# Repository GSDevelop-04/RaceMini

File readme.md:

<br />
<p align="center">
   
   <br/>
   Véhicule autonome au 1/10
   1/10 self driving car
</p>

##    1) Introduction

RaceMini est un véhicule au 1/10 d'étude sur la conduite autonome.
cliquer pour voir la vidéo sur youtube:

Le véhicule peut être piloté par un smartphone via une application Android et peut fonctionner en automatique ou manuel. Il utilise la reconnaissance des marquages au sol via la transformée de Hough sur une caméra openMV M7 ou H7 

<p align="center">
 
</p>

Le modèle est entierement imprimable en 3D

**Dans le dépot RaceMini vous trouverez :**

* les fichiers CAO, STL pour imprimantes 3D 20 x 20 cm ou 30 x 30 cm
* L'APK Android pour le téléphone
* Le source ESP32 pour IDE Arduino
* Le source Python pour L'OpenMV

Non obligatoire:
* Les fichiers kiCad pour la fabrication d'un circuit imprimé: il rationalise le câblage avec des connecteurs pour chaque élément du système ( carte variateur, alim 5V, camera, écran )
* Des examples de traitement de l'image (transformée de Hough et régréssion) en java script (juste pour comprendre, non utilisés dans RaceMini)

L'ensemble est sous licence **CC BY-NC-SA**

**Les éléments suivants sont nécessaires:**

* Caméra OpenMV H7 (M7 possible) **attention à l'objectif le 2,8 mm d'origine possède un champ de vision un peu limité préférer un 2 ou 2.2 mm**
* ESP32 ( Il existe de nombreux modules le CI est prévu pour un ESP32 DEVKIT V1: 30 broches)
* Carte variateur (la carte DRI0042 dispose d'une sortie 5V régulée)
* Moteur type 540 et Pignon moteur
* Un servomoteur
* batterie et interrupteur
* Visserie
* En option un écran Oled 1.3" monochrome **Attention selon le fabricant le GND et le 5V sont inversés !**

##    2) Structure matérielle.

<p align="center">
 
</p>

la carte ESP32 reçoit les informations des marquages au sol détectés par la caméra via une liaison série et commande le moteur via une carte variateur ainsi que le servomoteur de direction.  L'application Android permet de commander le véhicule en manuel et de passer en mode automatique. En mode automatique la vitesse maximale est aussi fixée par le téléphone. 

##    2.1) Traitement de l’image

Le traitement de l’image est effectué par le microcontrôleur STM32H7 de la camera open H7. Il comprend plusieurs parties :

**Sélection des zones d’intérêt :**
Toutes les zones de l’image ne présentent pas les mêmes intérêts : un virage au loin informe qu’il faudra diminuer la vitesse avant de l’aborder (cette zone n’est pas analyser dans la version actuelle), par contre, la zone immédiatement devant votre véhicule détermine l’action sur la direction. On défini trois zones d’intérêts :
* Zone d’anticipation (bleu) *(non utilisée dans la version actuelle)*
* Zone marquage au sol droit (jaune)
* Zone marquage au sol gauche(vert)

<p align="center">
 
</p>

Pour simplifier les zones sont rectangulaires et fixes.

* Détection des lignes dans les zones marquage au sol droit et gauche : L’algorithme utilise la transformée de Hough : chaque point sélectionné (contraste route grise et marquage blanc) sur l’écran est transformé en une sinusoïde représentant toutes les droites passant par ce point (distance de la droite par rapport à l’origine en fonction de l’angle de la droite) si plusieurs points sont alignés alors les sinusoïdes se croisent en un point image de la droite d’alignement. A l’issu de ce traitement on obtient un segment de droite pour le marquage au sol droit et un pour la gauche. Ils sont définis par les coordonnées (dans le repère de la camera) de leur extrémités.

NB : la transformée de Hough est une fonction déjà intégrée au Python de l’openMV mais un programme en javascript existe pour en comprendre le fonctionnement ( Attention les navigateurs Chrome, Firefox et le nouveau Edge -Chromium- ne supporte plus le traitement d'images sur disque, il faut charger la page html, le code javascript et l'image dans un serveur WEB)

* Calcul des segments dans le repère du véhicule à partir des coordonnées camera. Les points de la route sont supposés avoir une altitude nulle (terrain plat). Les quatre points sont ensuite transmis à l’ESP32 pour déterminer la conduite.

L’ensemble est programmé en python avec l’IDE openMV IDE.

##    2.2) Calcul de la commande de conduite.

La carte ESP32 reçoit les deux segments de droites des marquages au sol, elle détermine le CIR à partir de la médiane des deux segments (axe de la route) puis calcule la commande du servomoteur pour obtenir la bonne trajectoire :

L’ensemble est programmé dans l’IDE Arduino

<p align="center">
 
</p>

##    2.3) Câblage

**Liasons ESP32 Caméra:**  
* RX ESP32 (RX2) / Tx caméra (P1 uart 1 Tx)  
* TX ESP32 (TX2) / Rx caméra (P0 uart 1 RX)

**Liaisons ESP32 Variateur:**  
* ESP32 D25 / PWM 
* ESP32 D33 / IN2  // Marche avant: 1 Marche arrière: 0  
* ESP32 D32 / IN1  // Marche avant: 0 Marche arrière: 1

**Liaisons ESP32 Ecran:**  
* ESP32 D21 / OLED SDA  
* ESP32 D22 / OLED SCL
						
**Et les alimentations:** Le 5v est fourni par la carte variateur sinon utiliser un module regulateur 5V à découpage

##   3) Vidéos
* [Présentation: https://youtu.be/Jysb8A-HKZk](https://youtu.be/Jysb8A-HKZk)
* [Marquages au sol partie 1: https://youtu.be/zz7oVWdyysM](https://youtu.be/zz7oVWdyysM)
* [Marquages au sol partie 2: https://youtu.be/7tqPUZ-_XuY](https://youtu.be/7tqPUZ-_XuY)
* [Modélisation caméra sténopé: https://youtu.be/YC57ygDgGVU](https://youtu.be/YC57ygDgGVU)
* [Conduite: https://youtu.be/9OizZml_HDY](https://youtu.be/9OizZml_HDY)
* [RaceMaxi: https://youtu.be/luEXLeMDnMg](https://youtu.be/luEXLeMDnMg)

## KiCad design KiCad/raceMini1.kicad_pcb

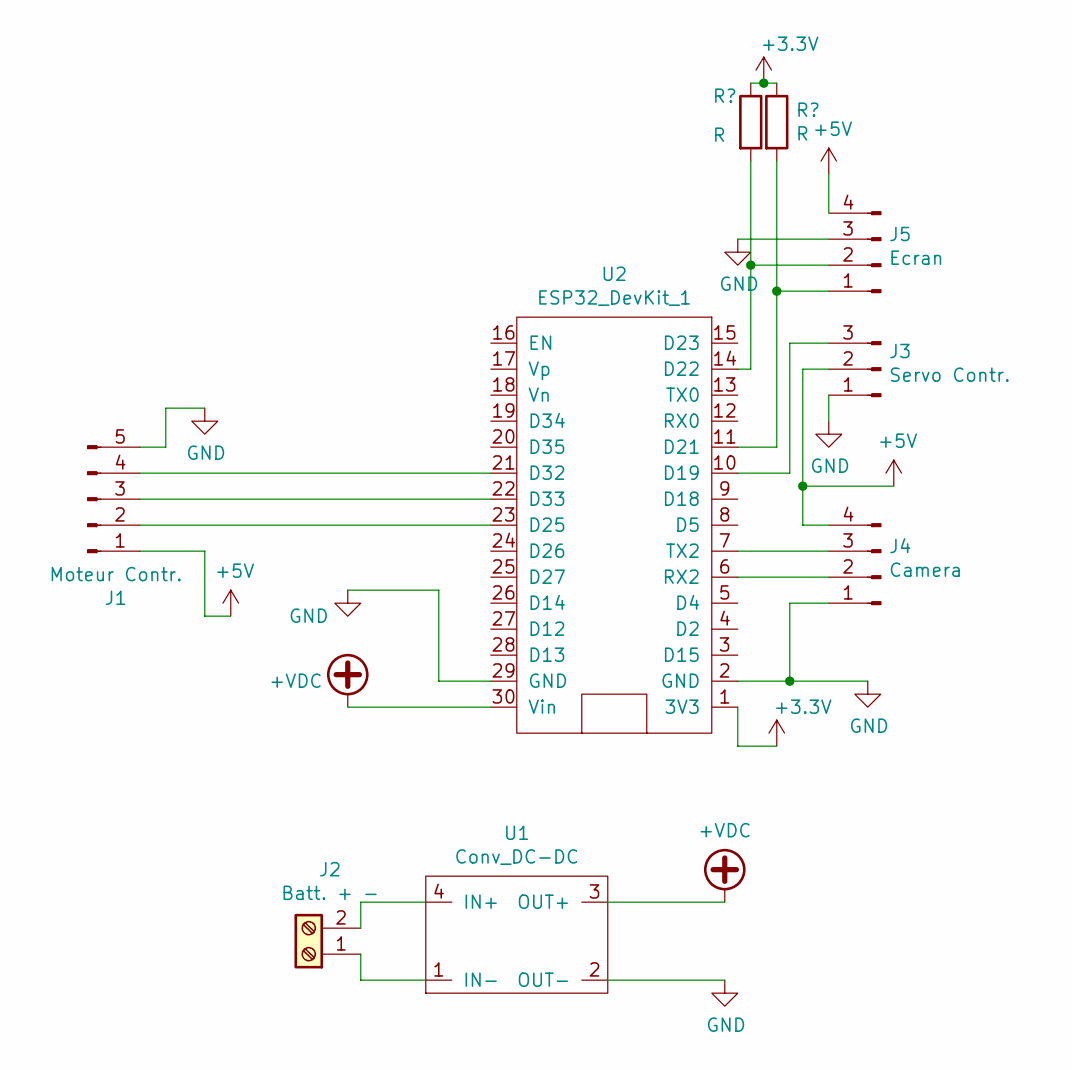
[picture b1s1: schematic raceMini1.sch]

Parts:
J1: Moteur Contr.; PinHeader_1x05_P2.54mm_Vertical
J2: Batt. + -; mkds_1,5-2
J3: Servo Contr.; PinHeader_1x03_P2.54mm_Vertical
J4: Camera; PinHeader_1x04_P2.54mm_Vertical
J5: Ecran; PinHeader_1x04_P2.54mm_Vertical
U1: Conv_DC-DC; Module_DC-DC_Lm2596
U2: ESP32_DevKit_1; ESP32_Devkit_DOIT_V1

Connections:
+5V: J1.1, J3.2, J4.4, J5.4
+VDC: U1.3 (OUT+), U2.30 (Vin)
GND: J1.5, J3.1, J4.1, J5.3, U1.2 (OUT-), U2.2 (GND), U2.29 (GND)
unnamed: J1.2, U2.23 (D25)
unnamed: J1.3, U2.22 (D33)
unnamed: J1.4, U2.21 (D32)
unnamed: J2.1, U1.1 (IN-)
unnamed: J2.2, U1.4 (IN+)
unnamed: J3.3, U2.10 (D19)
unnamed: J4.2, U2.6 (RX2)
unnamed: J4.3, U2.7 (TX2)
unnamed: J5.1, U2.11 (D21)
unnamed: J5.2, U2.14 (D22)

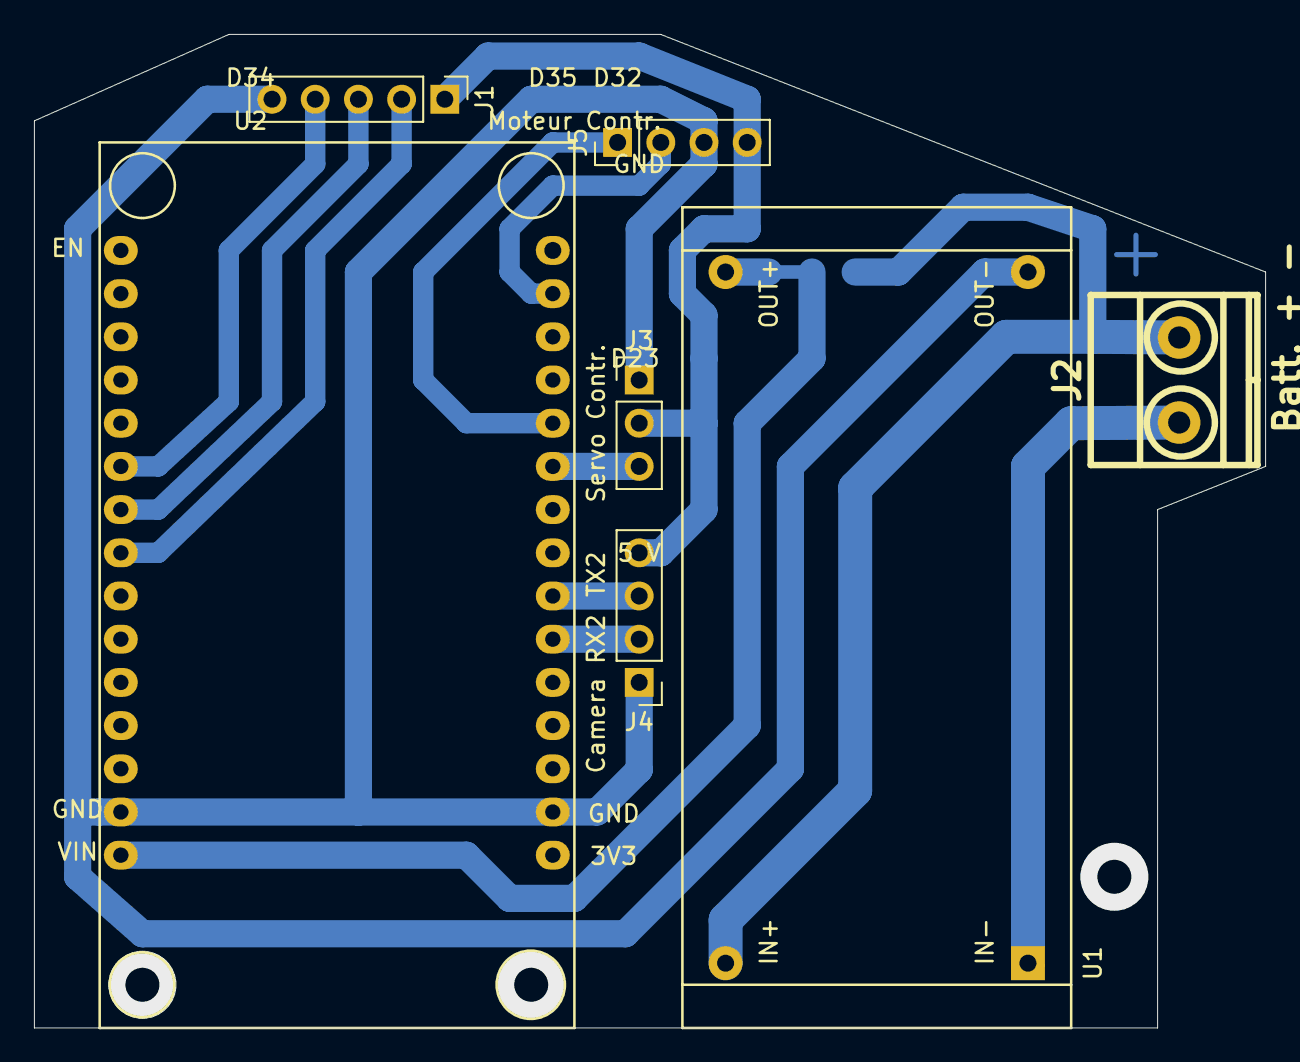
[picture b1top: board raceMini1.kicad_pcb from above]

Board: 2 copper layers, 72.4 x 58.4 mm, 7 parts (0 on the bottom side), 13 nets.

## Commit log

2020-12-21 premier commit
2020-12-21 présentation1
2020-12-22 Java et KiCad
2020-12-22 Maj suite erreurs
2020-12-22 imprimante 30 30
2020-12-22 Maj noms
2020-12-23 imprimante 20 20
